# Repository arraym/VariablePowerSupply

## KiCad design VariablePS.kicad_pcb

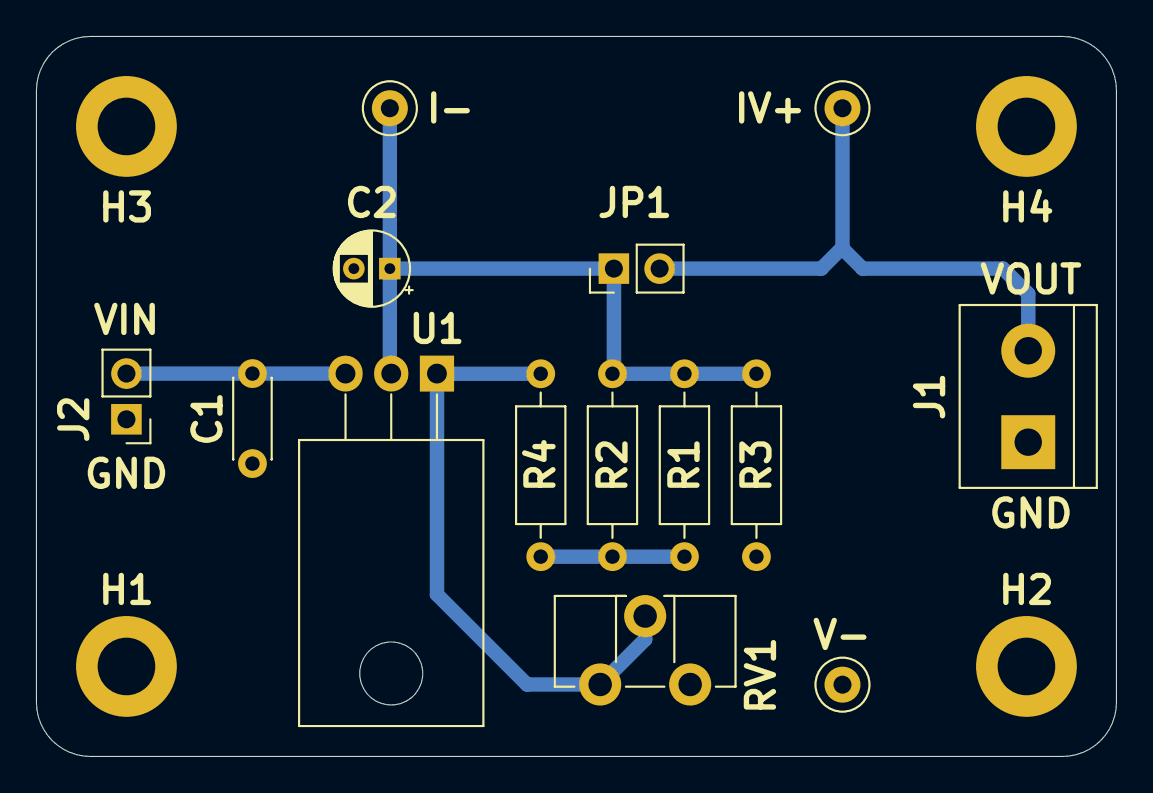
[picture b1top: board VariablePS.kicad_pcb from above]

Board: 2 copper layers, 60.0 x 40.0 mm, 18 parts (0 on the bottom side), 6 nets.

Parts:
C1: 100n; C_Disc_D4.3mm_W1.9mm_P5.00mm
C2: 2u2; CP_Radial_D4.0mm_P2.00mm
H1, H2, H3, H4: MH; MountingHole_3.2mm_M3_DIN965_Pad
I-: I-; TestPoint_Loop_D1.80mm_Drill1.0mm_Beaded
IV+: I+/V+; TestPoint_Loop_D1.80mm_Drill1.0mm_Beaded
J1: VOUT; TerminalBlock_bornier-2_P5.08mm
J2: VIN; PinHeader_1x02_P2.54mm_Vertical
JP1: Jumper; PinHeader_1x02_P2.54mm_Vertical
R1, R3, R4: 220R; R_Axial_DIN0207_L6.3mm_D2.5mm_P10.16mm_Horizontal
R2: DNP; R_Axial_DIN0207_L6.3mm_D2.5mm_P10.16mm_Horizontal
RV1: 1k; Potentiometer_ACP_CA9-H3,8_Horizontal
U1: LM317T; TO-220-3_Horizontal_TabDown
V-: V-; TestPoint_Loop_D1.80mm_Drill1.0mm_Beaded

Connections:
GND: C1.2, C2.2, H1.1, H2.1, H3.1, H4.1, J1.1, J2.1, R3.2, RV1.3, V-.1
unnamed: C1.1, J2.2, U1.3
unnamed: C2.1, I-.1, JP1.1, R1.1, R2.1, R3.1, U1.2
unnamed: IV+.1, J1.2, JP1.2
unnamed: R1.2, R2.2, R4.1
unnamed: R4.2, RV1.1, RV1.2, U1.1

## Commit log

2021-05-11 Initial Commit.
2021-05-11 PCB routing done, gerber files generated (v1.0).
